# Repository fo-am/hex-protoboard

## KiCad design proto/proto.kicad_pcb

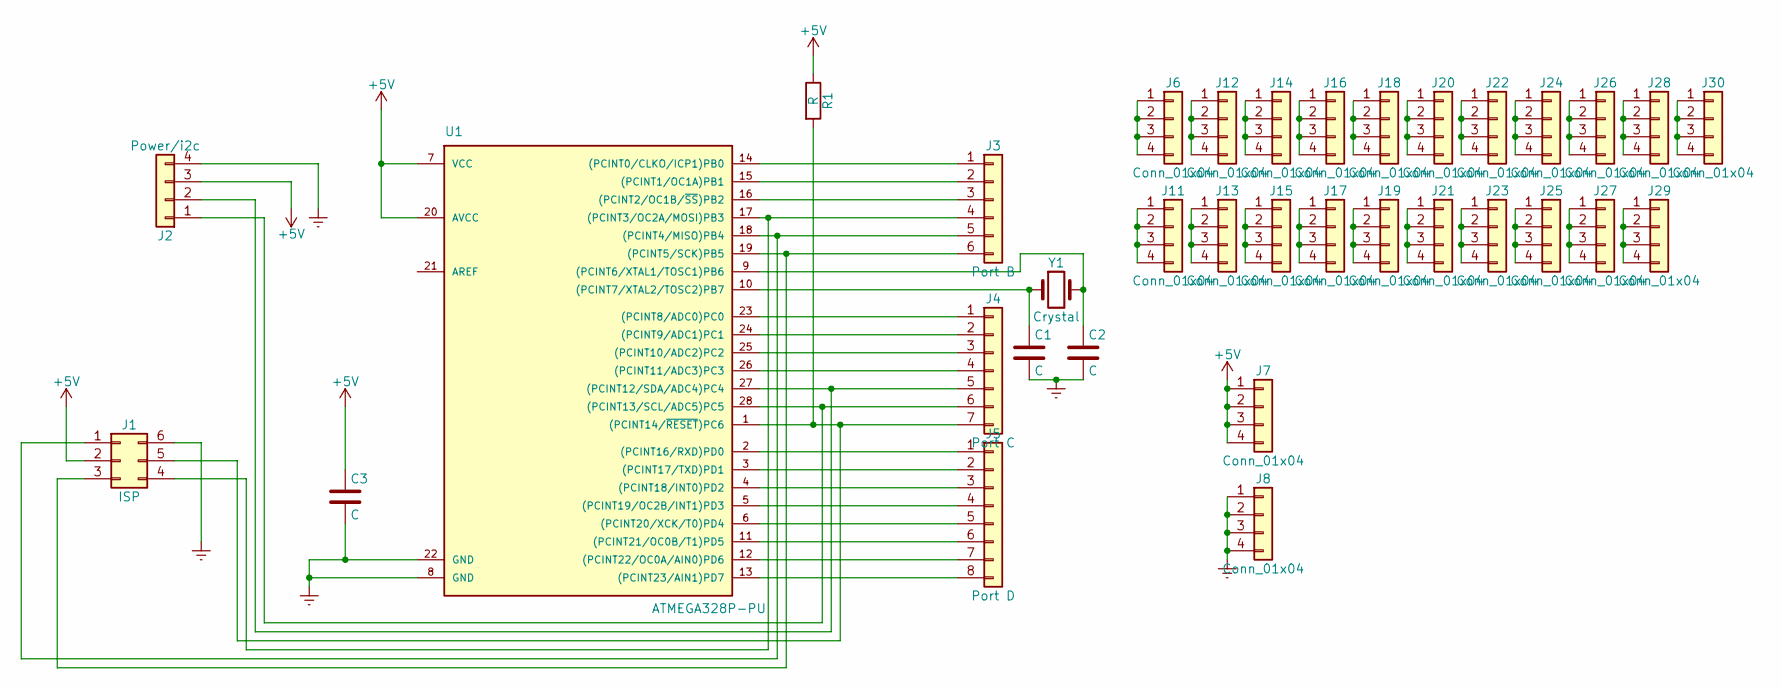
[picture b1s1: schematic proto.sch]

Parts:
C1, C2, C3: C; C_Disc_D3.0mm_W1.6mm_P2.50mm
J1: ISP; Pin_Header_Straight_2x03_Pitch2.54mm
J2: Power/i2c; Pin_Header_Straight_1x04_Pitch2.54mm
J3: Port B; Pin_Header_Straight_1x06_Pitch2.54mm
J4: Port C; Pin_Header_Straight_1x07_Pitch2.54mm
J5: Port D; Pin_Header_Straight_1x08_Pitch2.54mm
J6, J7, J8, J11, J12, J13, J14, J15, J16, J17, J18, J19, J20, J21, J22, J23, J24, J25, J26, J27, J28, J29, J30: Conn_01x04; Pin_Header_Straight_1x04_Pitch2.54mm
R1: R; R_Axial_DIN0204_L3.6mm_D1.6mm_P7.62mm_Horizontal
U1: ATMEGA328P-PU; DIP-28_W7.62mm
Y1: Crystal; Crystal_HC52-6mm_Vertical

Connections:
+5V: C3.1, J1.2, J2.3, J7.1, J7.2, J7.3, J7.4, R1.1, U1.7 (VCC), U1.20 (AVCC)
Earth: C1.2, C2.2, C3.2, J1.6, J2.4, J8.1, J8.2, J8.3, J8.4, U1.8 (GND), U1.22 (GND)
unnamed: C1.1, U1.10 ((PCINT7/XTAL2/TOSC2)PB7), Y1.1
unnamed: C2.1, U1.9 ((PCINT6/XTAL1/TOSC1)PB6), Y1.2
unnamed: J1.1, J3.5, U1.18 ((PCINT4/MISO)PB4)
unnamed: J1.3, J3.6, U1.19 ((PCINT5/SCK)PB5)
unnamed: J1.4, J3.4, U1.17 ((PCINT3/OC2A/MOSI)PB3)
unnamed: J1.5, J4.7, R1.2, U1.1 ((PCINT14/~RESET~)PC6)
unnamed: J2.1, J4.6, U1.28 ((PCINT13/SCL/ADC5)PC5)
unnamed: J2.2, J4.5, U1.27 ((PCINT12/SDA/ADC4)PC4)
unnamed: J3.1, U1.14 ((PCINT0/CLKO/ICP1)PB0)
unnamed: J3.2, U1.15 ((PCINT1/OC1A)PB1)
unnamed: J3.3, U1.16 ((PCINT2/OC1B/~SS~)PB2)
unnamed: J4.1, U1.23 ((PCINT8/ADC0)PC0)
unnamed: J4.2, U1.24 ((PCINT9/ADC1)PC1)
unnamed: J4.3, U1.25 ((PCINT10/ADC2)PC2)
unnamed: J4.4, U1.26 ((PCINT11/ADC3)PC3)
unnamed: J5.1, U1.2 ((PCINT16/RXD)PD0)
unnamed: J5.2, U1.3 ((PCINT17/TXD)PD1)
unnamed: J5.3, U1.4 ((PCINT18/INT0)PD2)
unnamed: J5.4, U1.5 ((PCINT19/OC2B/INT1)PD3)
unnamed: J5.5, U1.6 ((PCINT20/XCK/T0)PD4)
unnamed: J5.6, U1.11 ((PCINT21/OC0B/T1)PD5)
unnamed: J5.7, U1.12 ((PCINT22/OC0A/AIN0)PD6)
unnamed: J5.8, U1.13 ((PCINT23/AIN1)PD7)
unnamed: J6.1, J6.2, J6.3, J6.4
unnamed: J11.1, J11.2, J11.3, J11.4
unnamed: J12.1, J12.2, J12.3, J12.4
unnamed: J13.1, J13.2, J13.3, J13.4
unnamed: J14.1, J14.2, J14.3, J14.4
unnamed: J15.1, J15.2, J15.3, J15.4
unnamed: J16.1, J16.2, J16.3, J16.4
unnamed: J17.1, J17.2, J17.3, J17.4
unnamed: J18.1, J18.2, J18.3, J18.4
unnamed: J19.1, J19.2, J19.3, J19.4
unnamed: J20.1, J20.2, J20.3, J20.4
unnamed: J21.1, J21.2, J21.3, J21.4
unnamed: J22.1, J22.2, J22.3, J22.4
unnamed: J23.1, J23.2, J23.3, J23.4
unnamed: J24.1, J24.2, J24.3, J24.4
unnamed: J25.1, J25.2, J25.3, J25.4
unnamed: J26.1, J26.2, J26.3, J26.4
unnamed: J27.1, J27.2, J27.3, J27.4
unnamed: J28.1, J28.2, J28.3, J28.4
unnamed: J29.1, J29.2, J29.3, J29.4
unnamed: J30.1, J30.2, J30.3, J30.4

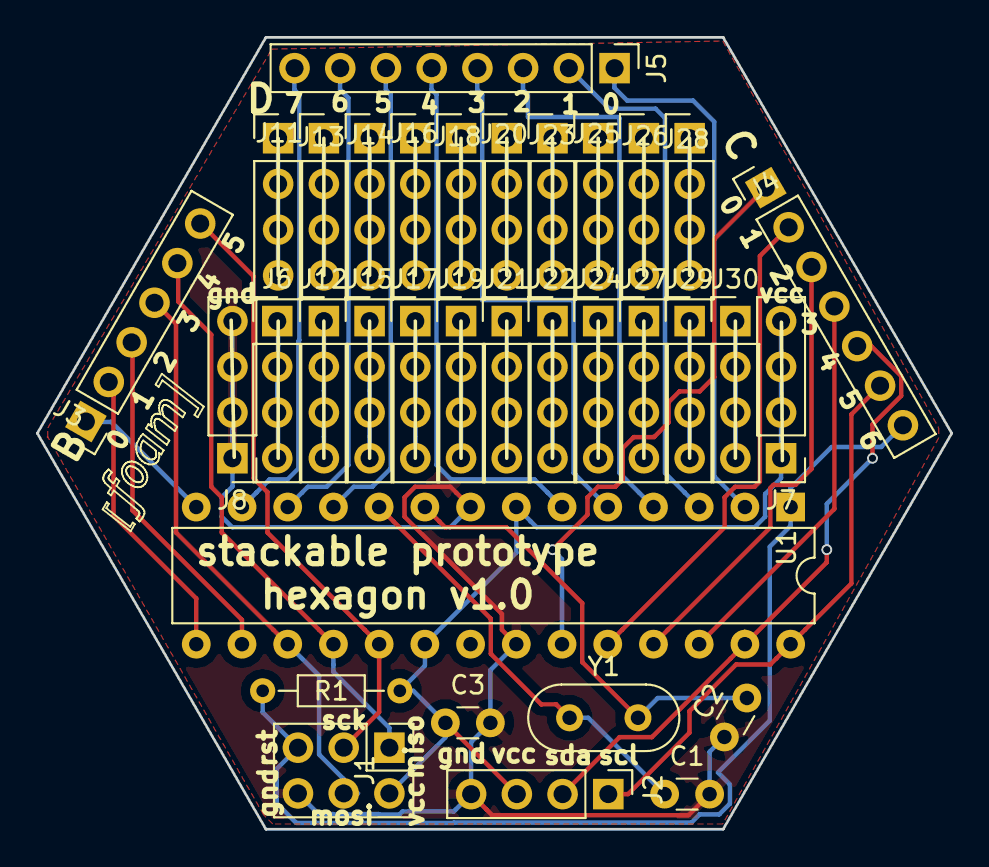
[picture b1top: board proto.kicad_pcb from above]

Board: 2 copper layers, 50.8 x 44.0 mm, 34 parts (0 on the bottom side), 46 nets.
